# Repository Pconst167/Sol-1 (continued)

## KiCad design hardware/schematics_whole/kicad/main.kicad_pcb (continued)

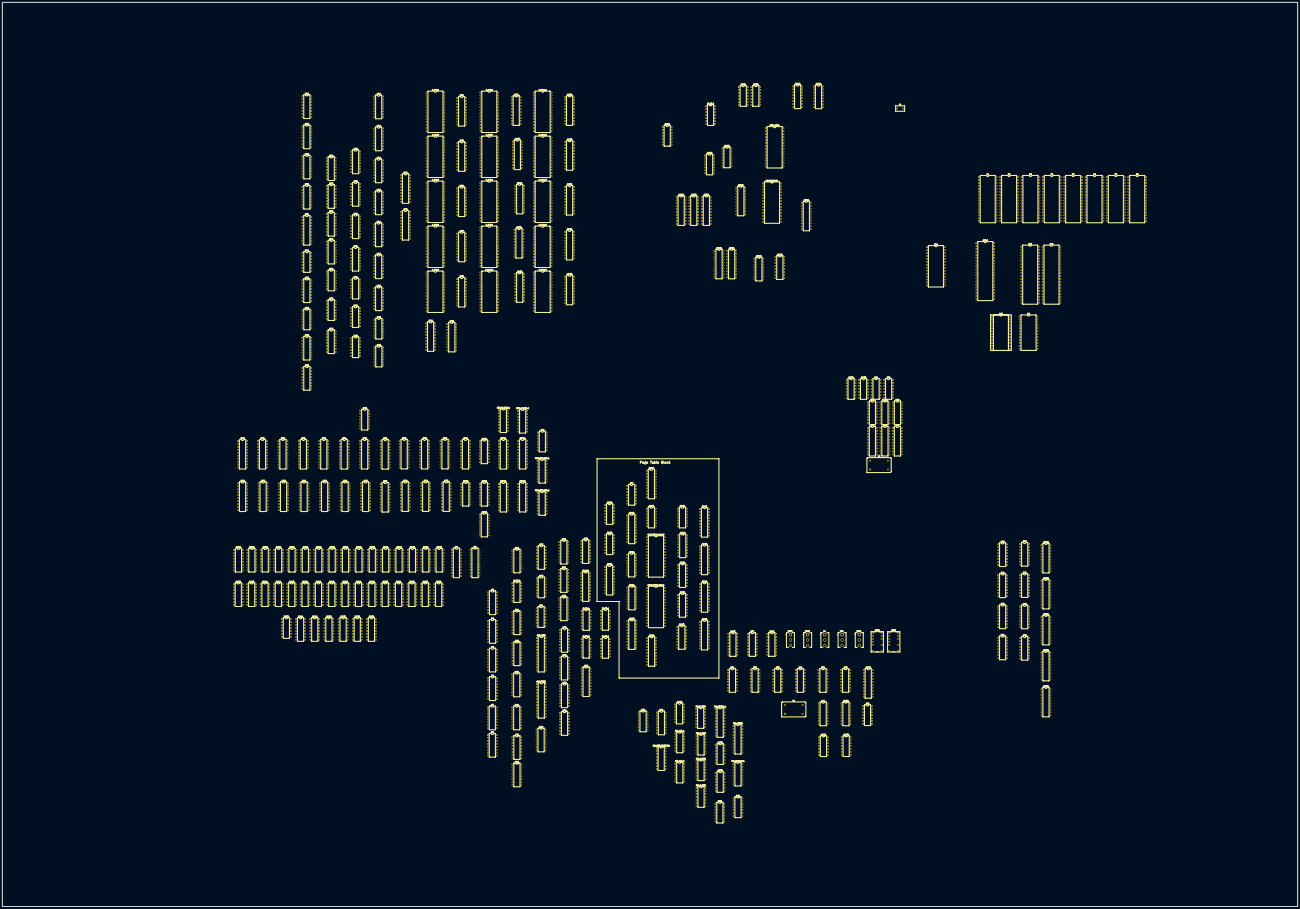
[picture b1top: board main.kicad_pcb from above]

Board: 2 copper layers, 1116.0 x 779.0 mm, 299 parts (0 on the bottom side), 1059 nets, no tracks yet.

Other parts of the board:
C1: C; C_Disc_D7.5mm_W4.4mm_P5.00mm
IC94, IC95: 74273N; DIP-20_W7.62mm
IC207, IC208: 7400N; DIP-14_W7.62mm

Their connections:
/int_status_0: IC207.2 (I1); also elsewhere on the board
/int_status_1: IC207.5 (I1); also elsewhere on the board
/int_status_2: IC207.10 (I1); also elsewhere on the board
/int_status_3: IC207.13 (I1); also elsewhere on the board
/int_status_4: IC208.2 (I1); also elsewhere on the board
/int_status_5: IC208.5 (I1); also elsewhere on the board
/int_status_6: IC208.10 (I1); also elsewhere on the board
/int_status_7: IC208.13 (I1); also elsewhere on the board
/irq_masks0: IC207.1 (I0); also elsewhere on the board
/irq_masks1: IC207.4 (I0); also elsewhere on the board
/irq_masks2: IC207.9 (I0); also elsewhere on the board
/irq_masks3: IC207.12 (I0); also elsewhere on the board
/irq_masks4: IC208.1 (I0); also elsewhere on the board
/irq_masks5: IC208.4 (I0); also elsewhere on the board
/irq_masks6: IC208.9 (I0); also elsewhere on the board
/irq_masks7: IC208.12 (I0); also elsewhere on the board
unnamed 536: IC94.3 (D1); also elsewhere on the board
unnamed 537: IC94.4 (D2); also elsewhere on the board
unnamed 538: IC94.7 (D3); also elsewhere on the board
unnamed 539: IC94.8 (D4); also elsewhere on the board
unnamed 540: IC94.13 (D5); also elsewhere on the board
unnamed 541: IC94.14 (D6); also elsewhere on the board
unnamed 542: IC94.17 (D7); also elsewhere on the board
unnamed 543: IC94.18 (D8); also elsewhere on the board
unnamed 544: IC95.3 (D1); also elsewhere on the board
unnamed 545: IC95.4 (D2); also elsewhere on the board
unnamed 546: IC95.7 (D3); also elsewhere on the board
unnamed 547: IC95.8 (D4); also elsewhere on the board
unnamed 548: IC95.13 (D5); also elsewhere on the board
unnamed 549: IC95.14 (D6); also elsewhere on the board
unnamed 550: IC95.17 (D7); also elsewhere on the board
cond_flag_src: IC95.6 (Q3); also elsewhere on the board
cond_invert: IC95.5 (Q2); also elsewhere on the board
cond_sel_0: IC95.9 (Q4); also elsewhere on the board
cond_sel_1: IC95.12 (Q5); also elsewhere on the board
cond_sel_2: IC95.15 (Q6); also elsewhere on the board
cond_sel_3: IC95.16 (Q7); also elsewhere on the board
rst: IC94.1 (CLR), IC95.1 (CLR); also elsewhere on the board
typ_0: IC94.2 (Q1); also elsewhere on the board
typ_1: IC94.5 (Q2); also elsewhere on the board
u_offset_0: IC94.6 (Q3); also elsewhere on the board
u_offset_1: IC94.9 (Q4); also elsewhere on the board
u_offset_2: IC94.12 (Q5); also elsewhere on the board
u_offset_3: IC94.15 (Q6); also elsewhere on the board
u_offset_4: IC94.16 (Q7); also elsewhere on the board
u_offset_5: IC94.19 (Q8); also elsewhere on the board
u_offset_6: IC95.2 (Q1); also elsewhere on the board
~clk: IC94.11 (CLK), IC95.11 (CLK); also elsewhere on the board

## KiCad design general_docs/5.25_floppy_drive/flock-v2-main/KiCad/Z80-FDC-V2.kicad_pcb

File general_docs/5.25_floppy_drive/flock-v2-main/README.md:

# Flock - Version 2.0
Floppy Disk Controller and Real Time Clock for RCBus systems

## Table of Content
* [Overview](#overview)
  * [Specifications](#specifications)
* [Assembly Instructions](#assembly-instructions)
* [Hardware Documentation](#hardware-documentation)
  * [Schematic and PCB Layout](#schematic-and-pcb-layout)
  * [Input/Output Ports](#inputoutput-ports)
  * [Connectors](#connectors)
  * [Bill of Materials](#bill-of-materials)
* [Release Notes](#release-notes)
  * [Changes](#changes)
  * [Known Issues](#known-issues)
* [Red Tape](#red-tape)
  * [Licensing](#licensing)
  * [Trademarks](#trademarks)

## Overview
Flock is an RCBus floppy disk controller (FDC) and real time clock (RTC) module. It designed to work with RomWBW firmware, supporting CP/M, ZSDOS, and various applications under these OSes.

### Specifications
* Floppy Disk Controller: Western Digital* WD37C65 or compatible
  * NEC uPD765 compatible with an integrated data separator, floppy interface drivers, and buffers
* Supported floppy disk formats:
  * 3.5", 720 KB
  * 3.5", 1.44 MB
  * 5.25", 360 KB diskettes in 360 MB drive
  * 5.25", 1.2 MB
  * 5.25", 360 KB diskettes in 1.2 MB drive (not supported by RomWBW, requires Y3, C10, and C11 to be installed)
* Supports two floppy drives, using IBM PC-like cable with twisted Disk Select / Motor Enable wires between two drives
* Real Time Clock: Maxim Integrated DS1302
* Bus: RCBus, RC2014* compatible

## Assembly Instructions

Please refer to [Assembly Instructions](Assembly_Instructions.md) document

## Hardware Documentation

### Schematic and PCB Layout

[Schematic - Version 2.0](KiCad/Z80-FDC-V2-Schematic-2.0.pdf)

[PCB Layout - Version 2.0](KiCad/Z80-FDC-V2-Board-2.0.pdf)

### Input/Output Ports

Flock uses the following I/O ports:

#### 0x48 - FDC CCR/DIR

Write: Floppy disk controller control configuration register (CCR)
Read: Floppy disk controller digital input register (DIR)

#### 0x50 - FDC MSR

Read: Floppy disk controller master status register (MSR)

#### 0x51 - FDC Data Register

Read/Write: Data from/to floppy disk controller

#### 0x58 - FDC DOR / TC

Write: Floppy disk controller digital output register (DOR)
Read: Toggle floppy disk controller transfer complete (TC) line

#### 0x0C or 0xC0 - RTC

Read/Write: Access real time clock (RTC)
The RTC address is configured using JP1 jumper

### Jumpers and Connectors

#### JP1 - RTC I/O address select

Position       | Description
-------------- | -----------------
open (default) | RTC address: 0xC0
closed         | RTC address: 0x0C

* Use 0xC0 address for Z80-based systems and 0x0C address for Z180-based systems

#### JP2 - Enable RTC

Position       | Description
-------------- | -----------------
1-2 (default)  | RTC enabled
2-3            | RTC disabled

* JP2 is a solder jumper, located on the back of the board
* By default positions 1-2 are connected with a PCB trace
* If the system already has an RTC or the RTC functionality is not needed:
  * Cut the PCB trace between positions 1-2
  * Connect positions 2-3 with a solder bridge

#### JP3 - Enable 300 Kbps transfer rate support

Position       | Description
-------------- | -----------------
1-2 (default)  | 300 Kbps disabled
2-3            | 300 Kbps enabled

* JP3 is a solder jumper, located on the back of the board
* By default positions 1-2 are connected with a PCB trace
* If 300 Kbps is desired:
  * Cut the PCB trace between positions 1-2
  * Connect positions 2-3 with a solder bridge
  * Install Y3, C10, and C11

#### J1 - Floppy
Connect to floppy drive interface connector.

Pin   | Signal Name | Description   | Pin   | Signal Name | Description
----- | ----------- | --------------| ----- | ----------- | -----------
J1-1  | GND         | Ground        | J1-2  | /DENSEL     | Density Select: 1 = Low density; 0 = High density
J1-3  | N/C         | Not connected | J1-4  | N/C         | Not connected
J1-5  | GND         | Ground        | J1-6  | N/C         | Not connected
J1-7  | GND         | Ground        | J1-8  | /INDEX      | Index hole: 0 = At the index hole
J1-9  | N/C         | Not connected | J1-10 | /MEA        | Motor Enable - Drive A
J1-11 | GND         | Ground        | J1-12 | /DSB        | Drive Select - Drive B
J1-13 | GND         | Ground        | J1-14 | /DSA        | Drive Select - Drive A
J1-15 | GND         | Ground        | J1-16 | /MEB        | Motor Enable - Drive B
J1-17 | N/C         | Not connected | J1-18 | /DIR        | Direction Select
J1-19 | GND         | Ground        | J1-20 | /STEP       | Head Step
J1-21 | GND         | Ground        | J1-22 | /WDATA      | Write Data
J1-23 | GND         | Ground        | J1-24 | /WE         | Write Enable: 0 = Write Enabled
J1-25 | GND         | Ground        | J1-26 | /TRK0       | Track 00: 0 = At the track 0
J1-27 | N/C         | Not connected | J1-28 | /WP         | Write Protect: 0 = Floppy disk is write protected
J1-29 | GND         | Ground        | J1-30 | /RDATA      | Read Data 
J1-31 | GND         | Ground        | J1-32 | /HDSEL      | Head Select / Side Select: 1 = Side 0; 0 = Side 1
J1-33 | N/C         | Not connected | J1-34 | /DC         | Disk changed: 1 = Disk changed; 0 = Ready

#### J2 - Floppy 5V
Connect to floppy 5V power supply connector.

**Important: J2 is an unfused 5V power supply for a single 3.5" floppy disk drive. Avoid overloading and short-circuiting**

Pin | Signal Name | Description
--- | ----------- | -----------
1   | 5V          | Positive terminal - +5V
2   | GND         | Negative terminal - ground

#### J3 - RCBus
Pin   | Signal Name | Description                             | Pin   | Signal Name | Description
----- | ----------- | --------------------------------------- | ----- | ----------- | -----------
J3-1  | A15         | Address A15; Input; Not connected       | J3-41 | p41         | Reserved; Not connected
J3-2  | A14         | Address A14; Input; Not connected       | J3-42 | /BAI        | Bus Acknowledge In; Not connected
J3-3  | A13         | Address A13; Input; Not connected       | J3-43 | /BAO        | Bus Acknowledge Out; Not connected
J3-4  | A12         | Address A12; Input; Not connected       | J3-44 | p44         | Reserved; Not connected
J3-5  | A11         | Address A11; Input; Not connected       | J3-45 | p45         | Reserved; Not connected
J3-6  | A10         | Address A10; Input; Not connected       | J3-46 | p46         | Reserved; Not connected
J3-7  | A9          | Address A9; Input; Not connected        | J3-47 | p47         | Reserved; Not connected
J3-8  | A8          | Address A8; Input; Not connected        | J3-48 | p48         | Reserved; Not connected
J3-9  | A7          | Address A7; Input                       | J3-49 | A23         | Address A23; Input; Not connected
J3-10 | A6          | Address A6; Input                       | J3-50 | A22         | Address A22; Input; Not connected
J3-11 | A5          | Address A5; Input                       | J3-51 | A21         | Address A21; Input; Not connected
J3-12 | A4          | Address A4; Input                       | J3-52 | A20         | Address A20; Input; Not connected
J3-13 | A3          | Address A3; Input                       | J3-53 | A19         | Address A19; Input; Not connected
J3-14 | A2          | Address A2; Input                       | J3-54 | A18         | Address A18; Input; Not connected
J3-15 | A1          | Address A1; Input                       | J3-55 | A17         | Address A17; Input; Not connected
J3-16 | A0          | Address A0; Input                       | J3-56 | A16         | Address A16; Input; Not connected
J3-17 | GND         | Ground                                  | J3-57 | GND         | Ground
J3-18 | VCC         | Power Supply - +5V                      | J3-58 | VCC         | Power Supply - +5V
J3-19 | /M1         | Machine Cycle One; Input                | J3-59 | /RFSH       | DRAM refresh; Input; Not connected
J3-20 | /RESET      | Reset; Input                            | J3-60 | PAGE        | Page ROM/RAM input; Not connected
J3-21 | CLK1        | CPU Clock; Input; Not connected         | J3-61 | CLK2        | UART Clock (programmable); Input; Not connected
J3-22 | /INT        | Interrupt; Output; Not connected        | J3-62 | /BUSACK     | DMA Bus Acknowledge; Input; Not connected
J3-23 | /MREQ       | Memory Request; Input; Not connected    | J3-63 | /HALT       | Halt; Input; Not connected
J3-24 | /WR         | Write Request; Input                    | J3-64 | /BUSREQ     | DMA Bus Request; Output; Not connected
J3-25 | /RD         | Read Request; Input                     | J3-65 | /WAIT       | Wait; Output; Not connected
J3-26 | /IORQ       | Input/Output Request; Input             | J3-66 | /NMI        | Non-maskable Interrupt; Output; Not connected
J3-27 | D0          | Data D0; Input/Output                   | J3-67 | D8          | Data D8; Input/Output; Not connected
J3-28 | D1          | Data D1; Input/Output                   | J3-68 | D9          | Data D9; Input/Output; Not connected
J3-29 | D2          | Data D2; Input/Output                   | J3-69 | D10         | Data D10; Input/Output; Not connected
J3-30 | D3          | Data D3; Input/Output                   | J3-70 | D11         | Data D11; Input/Output; Not connected
J3-31 | D4          | Data D4; Input/Output                   | J3-71 | D12         | Data D12; Input/Output; Not connected
J3-32 | D5          | Data D5; Input/Output                   | J3-72 | D13         | Data D13; Input/Output; Not connected
J3-33 | D6          | Data D6; Input/Output                   | J3-73 | D14         | Data D14; Input/Output; Not connected
J3-34 | D7          | Data D7; Input/Output                   | J3-74 | D15         | Data D15; Input/Output; Not connected
J3-35 | TX          | Channel 1, Transmit Data; Not Connected | J3-75 | TX2         | Channel 2, Transmit Data; Not Connected
J3-36 | RX          | Channel 1, Receive Data; Not Connected  | J3-76 | RX2         | Channel 2, Receive Data; Not Connected
J3-37 | /IRQ1       | Interrupt Request 1; Not connected      | J3-77 | /IRQ2       | Interrupt Request 2; Not connected
J3-38 | IEI         | Interrupt Enable In; Not connected      | J3-78 | p78         | Reserved; Not connected
J3-39 | IEO         | Interrupt Enable Out; Not connected     | J3-79 | p79         | Reserved; Not connected
J3-40 | USER4       | User Pin 4; Not connected               | J3-80 | USER8       | User Pin 8; Not connected

### Bill of Materials

#### Version 2.0

[Flock V2 project on Mouser.com](https://www.mouser.com/ProjectManager/ProjectDetail.aspx?AccessID=57797d9ea4) - View and order all components except of the FDC and the PCB.

[Flock project on OSH Park](https://oshpark.com/shared_projects/vQHiVNa8) - View and order the PCB.

Flock project on Tindie: [Complete kit](https://www.tindie.com/products/weird/flock-v2-rcbus-module-kit/); [Flock PCB and FDC](https://www.tindie.com/products/weird/flock-v2-rcbus-module-pcb-and-fdc/).

Component type     | Reference | Description                                 | Quantity | Possible sources and notes 
------------------ | --------- | ------------------------------------------- | -------- | --------------------------
PCB                |           | Flock PCB - Version 2.0                     | 1        | Buy from my Tindie store: [Complete kit](https://www.tindie.com/products/weird/flock-rcbus-v2-module-kit/); [Flock PCB and FDC](https://www.tindie.com/products/weird/flock-rcbus-v2-module-pcb-and-fdc/), or order from a PCB manufacturer of your choice using provided Gerber or KiCad files
Integrated Circuit | U1        | WD37C65BJM - FDC, CMOS, 44 pin PLCC         | 1        | eBay. Alternative: ST AIC37C65CL
Integrated Circuit | U2        | DS1302+ - RTC, 8 pin DIP                    | 1        | Mouser [700-DS1302](https://www.mouser.com/ProductDetail/700-DS1302)
Integrated Circuit | U3        | ATF16V8B-15PU - Simple Programmable Logic Device, 20 pin DIP | 1 | Mouser [556-AF16V8B15PU](https://www.mouser.com/ProductDetail/556-AF16V8B15PU)
Integrated Circuit | U4        | 74AHCT174 - Hex D-type flip-flop with reset, 16 pin DIP | 1 | Mouser [595-SN74AHCT174N](https://www.mouser.com/ProductDetail/595-SN74AHCT174N)
Integrated Circuit | U5        | 74HCT125 - Quadruple bus buffer gates with 3-state outputs, 14 pin DIP | 1 | Mouser [595-SN74HCT125NE4](https://www.mouser.com/ProductDetail/595-SN74HCT125NE4)
Quartz Crystal     | Y1        | 16 MHz, series                              | 1        | Mouser [774-ATS160-E](https://www.mouser.com/ProductDetail/774-ATS160-E)
Quartz Crystal     | Y2        | 32768 Hz, 6 pF                              | 1        | Mouser [815-AB26T32768KHZ6B](https://www.mouser.com/ProductDetail/815-AB26T32768KHZ6B)
Quartz Crystal     | Y3        | 9.6 MHz, series                             | 1        | Optional; Install for 300 Kbps transfer rate support
Connector          | J1        | 2x17 pin header, shrouded, 2.54 mm pitch, right angle | 1 | Mouser [517-30334-5002](https://www.mouser.com/ProductDetail/517-30334-5002)
Connector          | J2        | 2 pin header with friction lock, right angle | 1       | Mouser [571-2-644488-2](https://www.mouser.com/ProductDetail/571-2-644488-2)
Pin Header         | J3        | 2x40 pin header, 2.54 mm pitch, right angle | 1        | Mouser [517-5121TG](https://www.mouser.com/ProductDetail/517-5121TG)
Pin Header         | JP1       | 2 pin header, 2.54 mm pitch                 | 1        | Mouser [649-68002-102HLF](https://www.mouser.com/ProductDetail/649-68002-102HLF)
Jumper             | JP1       | Shunt, 2 pin 2.54 mm pitch                  | 1        | Mouser [806-SX1100-B](https://www.mouser.com/ProductDetail/806-SX1100-B)
Battery Holder     | BT1       | CR2032 battery holder                       | 1        | Mouser [122-2620-GR](https://www.mouser.com/ProductDetail/122-2620-GR) or [122-2420-GR](https://www.mouser.com/ProductDetail/122-2420-GR). Install either BT1 or C7
Battery            | BT1       | CR2023 battery                              | 1        | Mouser [81-CR2032](https://www.mouser.com/ProductDetail/81-CR2032), [658-CR2032](https://www.mouser.com/ProductDetail/658-CR2032), or [614-CR2032-200](https://www.mouser.com/ProductDetail/614-CR2032-200). Install either BT1 or C7
Capacitor          | C1 - C5   | 0.1 uF, 50V, MLCC, 5 mm pitch               | 5        | Mouser [810-FG28X7R1H104KNT6](https://www.mouser.com/ProductDetail/810-FG28X7R1H104KNT6)
Capacitor          | C6        | 10 uF, 47V, Organic Polymer, 6.3 mm diameter, 2.5 mm pitch | 1 | Mouser [80-A759EA106M1JAAE60](https://www.mouser.com/ProductDetail/80-A759EA106M1JAAE60). Note: PCB silkscreen specifies 47uF capacitor. 10uF - 47uF capacitor with voltage rating 10V or more can be used
Capacitor          | C7        | 0.22 F, 5.5V, Supercapacitor, 13.5 mm diameter, 5 mm pitch | 1 | Mouser [555-DBN-5R5D334T](https://www.mouser.com/ProductDetail/555-DBN-5R5D334T). Install either BT1 or C7
Capacitor          | C8        | 47 pF, 50V, MLCC, 5 mm pitch                | 1        | Mouser [810-FG28C0G2A470JNT0](https://www.mouser.com/ProductDetail/810-FG28C0G2A470JNT0)
Capacitor          | C9        | 15 pF, 50V, MLCC, 5 mm pitch                | 1        | Mouser [810-FG28C0G2A150JNT0](https://www.mouser.com/ProductDetail/810-FG28C0G2A150JNT0)
Capacitor          | C10       | 68 pF, 50V, MLCC, 5 mm pitch                | 1        | Optional; Install for 300 Kbps transfer rate support
Capacitor          | C11       | 56 pF, 50V, MLCC, 5 mm pitch                | 1        | Optional; Install for 300 Kbps transfer rate support
Resistor Array     | RN1       | 1 kohm, bussed, 6 pin SIP                   | 1        | Mouser [652-4606X-1LF-1K](https://www.mouser.com/ProductDetail/652-4606X-1LF-1K)
Resistor           | R1 - R3   | 10 kohm, 0.25 W, 1% tolerance, axial        | 3        | Mouser [603-MFR-25FRF5210K](https://www.mouser.com/ProductDetail/603-MFR-25FRF5210K)
IC Socket          | U1        | 44 pin PLCC, through hole                   | 1        | Mouser [649-54020-44030LF](https://www.mouser.com/ProductDetail/649-54020-44030LF), [517-8444-11B1-RK-TP](https://www.mouser.com/ProductDetail/517-8444-11B1-RK-TP)
IC Socket          | U2        | 8 pin DIP                                   | 1        | Mouser [649-DILB8P223TLF](https://www.mouser.com/ProductDetail/649-DILB8P223TLF)
IC Socket          | U3        | 20 pin DIP                                  | 1        | Mouser [649-DILB20P-223TLF](https://www.mouser.com/ProductDetail/649-DILB20P-223TLF)
IC Socket          | U4        | 16 pin DIP                                  | 1        | Mouser [649-DILB16P-223TLF](https://www.mouser.com/ProductDetail/649-DILB16P-223TLF)
IC Socket          | U5        | 14 pin DIP                                  | 1        | Mouser [649-DILB14P-223TLF](https://www.mouser.com/ProductDetail/649-DILB14P-223TLF)
Connector          | J2        | 2 pin connector                             | 1        | Mouser [571-3-643813-2](https://www.mouser.com/ProductDetail/571-3-643813-2)
Connector          | J2        | Floppy disk power connector housing         | 1        | Mouser [571-1718224](https://www.mouser.com/ProductDetail/571-1718224)
Connector          | J2        | Floppy disk power connector contacts        | 2        | Mouser [571-170262-2-LP](https://www.mouser.com/ProductDetail/571-170262-2-LP), [571-1702622-CT](https://www.mouser.com/ProductDetail/571-1702622-CT) (strip of 100 contacts)

## Release Notes

### Changes

* Version 2.0
  * Update form factor from RC2014* compatible to RCBus
  * Add an option to use CR2032 battery instead of a super capacitor for the RTC
  * Use right angle connector for the floppy interface
  * Use ATF16V8B SPLD for address decode
  * Add JP1 jumper for selecting RTC I/O address. Either 0xC0 or 0x0C can be used
  * Add JP2 jumper for disabling the RTC.
  * Add an option to support 300 Kbps transfer speed
  * Add a header for GPIO signals
* Version 1.0
  * Initial version

### Known Issues

* Version 1.0
  * No known issues

### Wishlist
* None so far

## Red Tape

### Licensing

Flock is an open source hardware project certified by [Open Source Hardware Association](https://www.oshwa.org/), certification UID is [US002115](https://certification.oshwa.org/us002115.html). The hardware design itself, including schematic and PCB layout design files are licensed under the strongly-reciprocal variant of [CERN Open Hardware Licence version 2](license-cern_ohl_s_v2.txt). The CPLD VHDL code is licensed under [GNU General Public License v3](license-gpl-3.0.txt). Documentation, including this file, is licensed under the [Creative Commons Attribution-ShareAlike 4.0 International License](license-cc-by-sa-4.0.txt).

### Trademarks

* "RC2014" is a registered trademark of RFC2795 Ltd.
* Other names and brands may be claimed as the property of others.

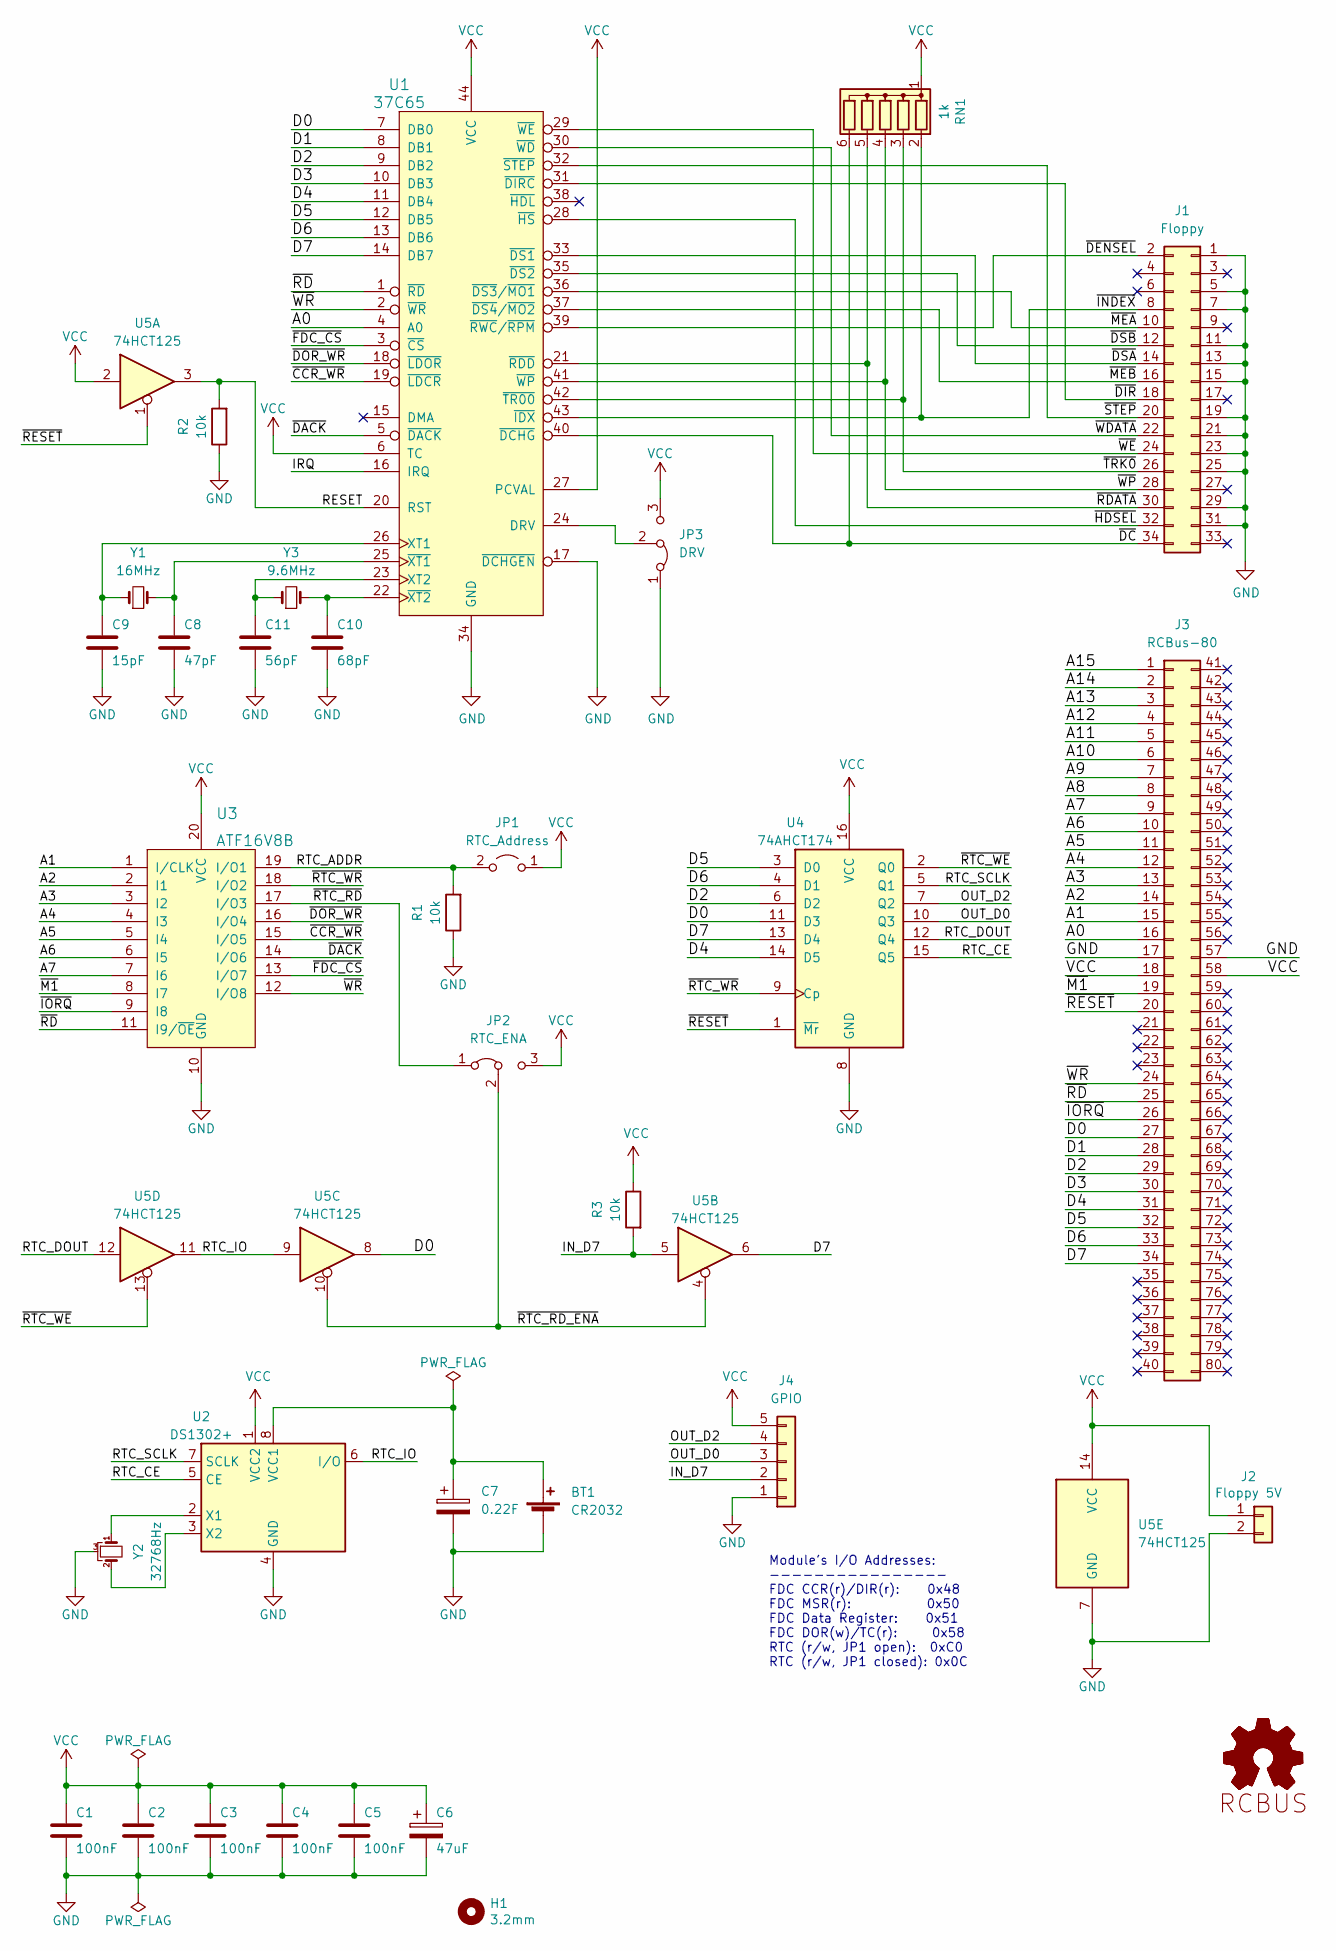
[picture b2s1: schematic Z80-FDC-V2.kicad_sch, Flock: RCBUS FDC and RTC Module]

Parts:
BT1: CR2032; Battery_Holder_CR2032_Universal
C1, C2, C3, C4, C5: 100nF; Cap_Cer_508
C6: 47uF; Cap_Elec_Radial_6.3mm
C7: 0.22F; Cap_Super_Radial_13.5mm
C8: 47pF; Cap_Cer_508
C9: 15pF; Cap_Cer_508
C10: 68pF; Cap_Cer_508
C11: 56pF; Cap_Cer_508
H1: 3.2mm; MountingHole_3.2mm_M3_DIN965
J1: Floppy; Conn_Pin_Header_17x2_2.54mm_Shrouded_RA
J2: Floppy 5V; Conn_TE_2-644488-2_2P_2.54mm
J3: RCBus-80; Conn_Pin_Header_40x2_2.54mm_Right_Angle_RCBus80
J4: GPIO; Conn_Pin_Header_5x1_2.54mm
JP1: RTC_Address; Conn_Pin_Header_2x1_2.54mm_NoKey
JP2: RTC_ENA; SolderJumper-3_P1.3mm_Bridged12_RoundedPad1.0x1.5mm_NumberL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
JP3: DRV; SolderJumper-3_P1.3mm_Bridged12_RoundedPad1.0x1.5mm_NumberL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
LOGO1, LOGO2: Logo_Open_Hardware_Small; OSHW-Logo_5.7x6mm_SilkScreen
LOGO3: RCBUS_Logo
R1, R2, R3: 10k; Res_762
RN1: 1k; Conn_SIL6
U1: 37C65; IC_PLCC44_TH
U2: DS1302+; IC_DIP8_300
U3: ATF16V8B; IC_DIP20_300
U4: 74AHCT174; IC_DIP16_300
U5: 74HCT125; IC_DIP14_300
Y1: 16MHz; Crystal_HC-49U_Vert
Y2: 32768Hz; Crystal_32K_Horiz
Y3: 9.6MHz; Crystal_HC-49U_Vert

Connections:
/A0: J3.16, U1.4 (A0)
/A1: J3.15, U3.1 (I/CLK)
/A2: J3.14, U3.2 (I1)
/A3: J3.13, U3.3 (I2)
/A4: J3.12, U3.4 (I3)
/A5: J3.11, U3.5 (I4)
/A6: J3.10, U3.6 (I5)
/A7: J3.9, U3.7 (I6)
/A8: J3.8
/A9: J3.7
/A10: J3.6
/A11: J3.5
/A12: J3.4
/A13: J3.3
/A14: J3.2
/A15: J3.1
/D0: J3.27, U1.7 (DB0), U4.11 (D3), U5.8
/D1: J3.28, U1.8 (DB1)
/D2: J3.29, U1.9 (DB2), U4.6 (D2)
/D3: J3.30, U1.10 (DB3)
/D4: J3.31, U1.11 (DB4), U4.14 (D5)
/D5: J3.32, U1.12 (DB5), U4.3 (D0)
/D6: J3.33, U1.13 (DB6), U4.4 (D1)
/D7: J3.34, U1.14 (DB7), U4.13 (D4), U5.6
/IN_D7: J4.2, R3.2, U5.5
/IRQ: U1.16 (IRQ)
/OUT_D0: J4.3, U4.10 (Q3)
/OUT_D2: J4.4, U4.7 (Q2)
/RESET: R2.2, U1.20 (RST), U5.3
/RTC_ADDR: JP1.2 (B), R1.2, U3.19 (I/O1)
/RTC_CE: U2.5 (CE), U4.15 (Q5)
/RTC_DOUT: U4.12 (Q4), U5.12
/RTC_IO: U2.6 (I/O), U5.9, U5.11
/RTC_SCLK: U2.7 (SCLK), U4.5 (Q1)
/~CCR_WR: U1.19 (~LDCR), U3.15 (I/O5)
/~DACK: U1.5 (~DACK), U3.14 (I/O6)
/~DC: J1.34, RN1.6 (R5), U1.40 (~DCHG)
/~DENSEL: J1.2, U1.39 (~RWC/~RPM)
/~DIR: J1.18, U1.31 (~DIRC)
/~DOR_WR: U1.18 (~LDOR), U3.16 (I/O4)
/~DSA: J1.14, U1.33 (~DS1)
/~DSB: J1.12, U1.35 (~DS2)
/~FDC_CS: U1.3 (~CS), U3.13 (I/O7)
/~HDSEL: J1.32, U1.28 (~HS)
/~INDEX: J1.8, RN1.2 (R1), U1.43 (~IDX)
/~IORQ: J3.26, U3.9 (I8)
/~M1: J3.19, U3.8 (I7)
/~MEA: J1.10, U1.36 (~DS3/~MO1)
/~MEB: J1.16, U1.37 (~DS4/~MO2)
/~RDATA: J1.30, RN1.5 (R4), U1.21 (~RDD)
/~RD: J3.25, U1.1 (~RD), U3.11 (I9/~OE)
/~RESET: J3.20, U4.1 (~Mr), U5.1
/~RFSH: J3.59
/~RTC_RD_ENA: JP2.2 (C), U5.4, U5.10
/~RTC_RD: JP2.1 (A), U3.17 (I/O3)
/~RTC_WE: U4.2 (Q0), U5.13
/~RTC_WR: U3.18 (I/O2), U4.9 (Cp)
/~STEP: J1.20, U1.32 (~STEP)
/~TRK0: J1.26, RN1.3 (R2), U1.42 (~TR00)
/~WDATA: J1.22, U1.30 (~WD)
/~WE: J1.24, U1.29 (~WE)
/~WP: J1.28, RN1.4 (R3), U1.41 (~WP)
/~WR: J3.24, U1.2 (~WR), U3.12 (I/O8)
GND: BT1.2 (-), C1.2, C2.2, C3.1, C4.2, C5.2, C6.2, C7.2, C8.2, C9.2, C10.2, C11.2, J1.1, J1.5, J1.7, J1.11, J1.13, J1.15, J1.19, J1.21, J1.23, J1.25, J1.29, J1.31, J2.2, J3.17, J3.57, J4.1, JP3.1 (A), R1.1, R2.1, U1.17 (~DCHGEN), U1.34 (GND), U2.4 (GND), U3.10 (GND), U4.8 (GND), U5.7 (GND), Y2.3
unnamed: BT1.1 (+), C7.1, U2.8 (VCC1)
unnamed: C8.1, U1.25 (~XT1), Y1.2
unnamed: C9.1, U1.26 (XT1), Y1.1
unnamed: C10.1, U1.22 (~XT2), Y3.2
unnamed: C11.1, U1.23 (XT2), Y3.1
unnamed: JP3.2 (C), U1.24 (DRV)
unnamed: U2.2 (X1), Y2.1
unnamed: U2.3 (X2), Y2.2
VCC: C1.1, C2.1, C3.2, C4.1, C5.1, C6.1, J2.1, J3.18, J3.58, J4.5, JP1.1 (A), JP2.3 (B), JP3.3 (B), R3.1, RN1.1 (common), U1.6 (TC), U1.27 (PCVAL), U1.44 (VCC), U2.1 (VCC2), U3.20 (VCC), U4.16 (VCC), U5.2, U5.14 (VCC)

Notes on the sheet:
Module's I/O Addresses: ---------------- FDC CCR(r)/DIR(r): 0x48 FDC MSR(r): 0x50 FDC Data Register: 0x51 FDC DOR(w)/TC(r): 0x58 RTC (r/w, JP1 open): 0xC0 RTC (r/w, JP1 closed): 0x0C

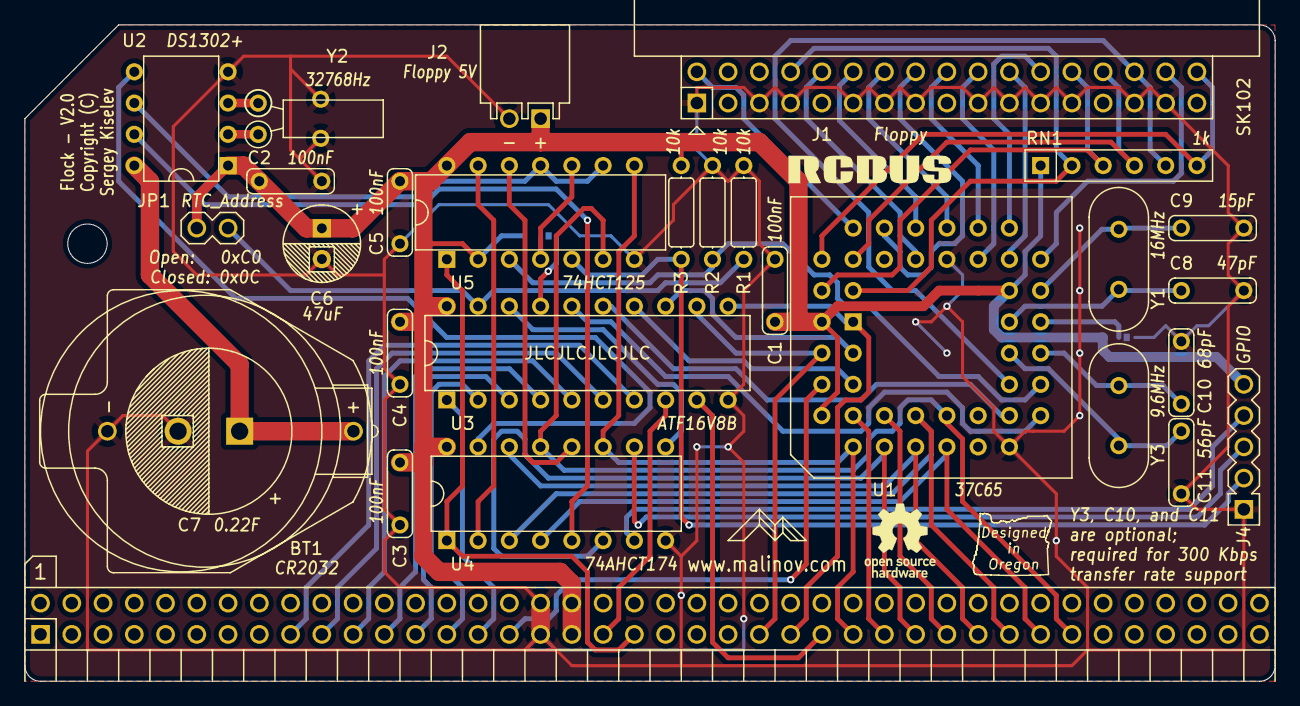
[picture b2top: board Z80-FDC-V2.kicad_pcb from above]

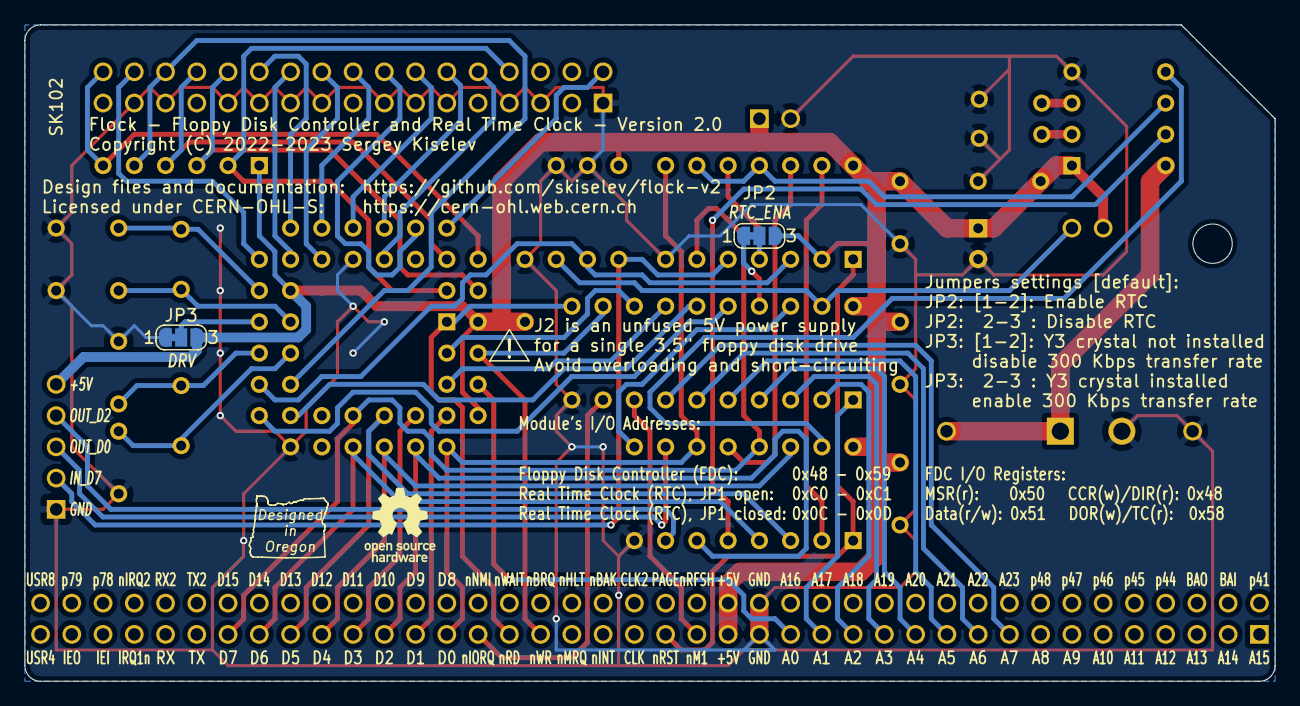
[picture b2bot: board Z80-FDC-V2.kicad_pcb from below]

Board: 2 copper layers, 101.6 x 53.3 mm, 35 parts (3 on the bottom side), 63 nets.

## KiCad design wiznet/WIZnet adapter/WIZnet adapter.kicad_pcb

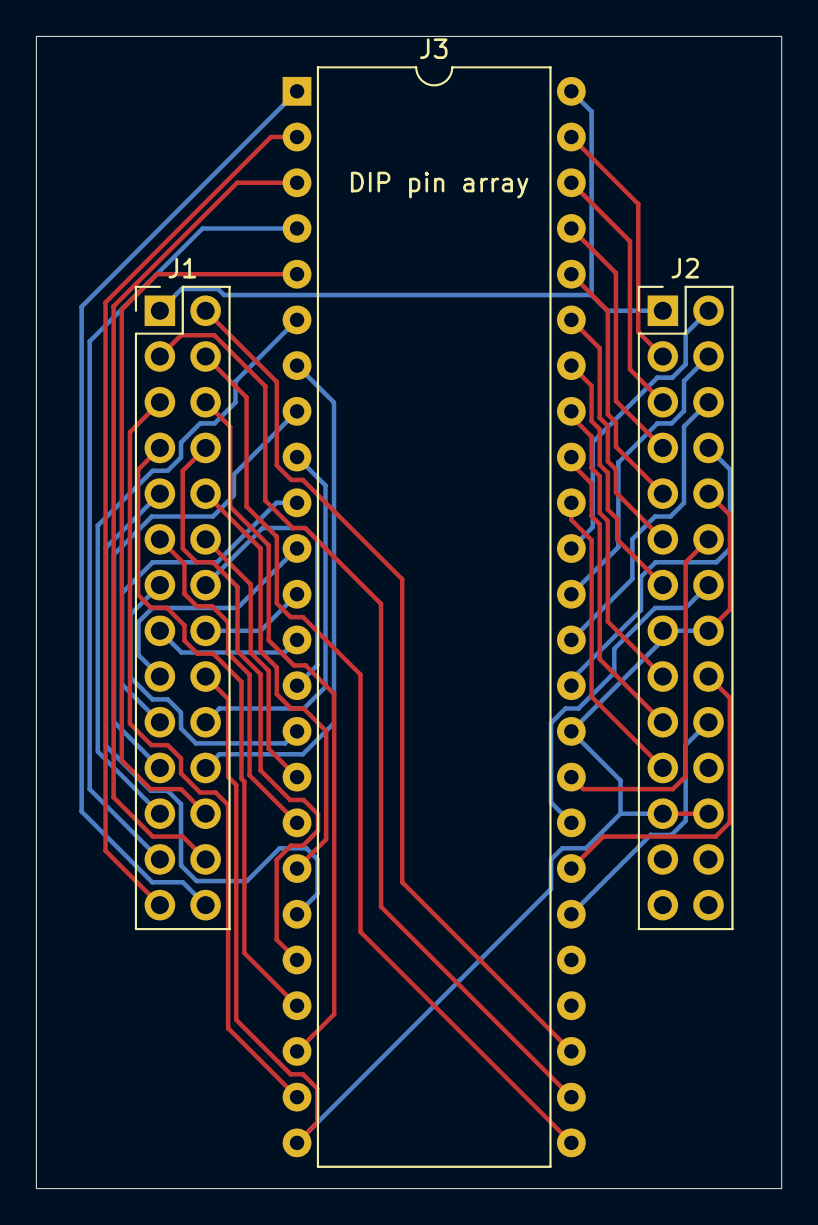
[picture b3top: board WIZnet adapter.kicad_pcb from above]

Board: 2 copper layers, 41.4 x 64.0 mm, 3 parts (0 on the bottom side), 45 nets.

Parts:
J1, J2: Conn_02x14_Odd_Even; PinHeader_2x14_P2.54mm_Vertical
J3: DIP pin array; DIP-48_W15.24mm

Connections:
A0: J1.28, J3.1
A1: J1.27, J3.2
A2: J1.26, J3.3
A3: J1.25, J3.4
A4: J1.24, J3.5
A5: J1.23, J3.6
A6: J1.22, J3.7
A7: J1.21, J3.8
A8: J1.20, J3.9
A9: J1.19, J3.10
BIT16EN: J2.2, J3.38
BRDY0: J2.14, J3.32
BRDY1: J2.13, J3.42
BRDY2: J2.12, J3.33
BRDY3: J2.11, J3.43
D0: J1.17, J3.11
D1: J1.16, J3.12
D2: J1.15, J3.13
D3: J1.14, J3.14
D4: J1.13, J3.15
D5: J1.12, J3.16
D6: J1.11, J3.17
D7: J1.10, J3.18
D8: J1.9, J3.19
D9: J1.8, J3.20
D10: J1.7, J3.21
D11: J1.6, J3.22
D12: J1.5, J3.23
D13: J1.4, J3.25
D14: J1.3, J3.26
D15: J1.2, J3.27
GND: J1.18, J2.10, J2.15, J2.16, J2.23, J2.24, J3.24, J3.34
Vcc: J1.1, J2.1, J3.48
~ACTLED: J2.9, J3.44
~COLLED: J2.6, J3.36
~CS: J2.19, J3.40
~FDXLED: J2.7, J3.45
~INT: J2.18, J3.31
~LINKLED: J2.3, J3.47
~RD: J2.20, J3.30
~RESET: J2.17, J3.41
~RXLED: J2.5, J3.46
~SPDLED: J2.8, J3.35
~TXLED: J2.4, J3.37
~WR: J2.21, J3.39

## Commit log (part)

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2024-06-24 micro
2024-06-25 sand32 sor32 add32 adc32 sub32 sbb32 and others added
2024-06-28 fix sor/sand.
2024-06-28 fix shl32
2024-06-28 add cmp32 cb, i32
2024-06-28 working on 32bit inc/dec
2024-07-06 socat
2024-07-06 software
2024-07-06 soft
2024-07-14 cleanup
2024-07-15 added notes
2024-07-16 floppy docs
2024-07-16 add vm fig
2024-07-16 added inline asm
2024-07-16 update schem
2024-07-16 floppy
2024-07-17 docs
2024-07-17 change dirs
2024-07-17 added various games
2024-07-17 adding smallc and cpm to misc
2024-07-18 add tms2797 datasheet
2024-07-18 writing list of sol-1 cpu improvements for next version
2024-07-18 flppy
2024-07-22 floppy notes
2024-07-25 notes
2024-08-19 floppy drive
2024-10-03 esp8266
2024-10-25 fpu updates
2025-11-23 nothing
2025-12-13 for post inc/dec the var address was being generated twice. removed one of the generations.
2025-12-24 adding note about fs
2025-12-28 file system ext2
2026-01-02 adding new bootloader for ext2 fs
2026-01-02 adding new kernel for ext2 fs
2026-01-06 ext2
2026-01-08 start work on ls syscall
2026-01-08 adding comment
2026-01-11 fixing calculation for inode sector and offet
2026-01-13 adding attribute to struct to remove padding
2026-01-13 adding attribute to remove padding
2026-01-13 renaming files
2026-01-13 add comments
2026-01-16 fixing bug on kernel loading
2026-01-18 hurry and commit thisgit add -A! after 2 days debugging i find my code misbehaves because of single offset bytes generated by solfs.
2026-01-22 software build script moves .exp to ./lib
2026-01-22 adding comments for process/file descriptors
2026-01-22 add uart1
2026-01-23 add kernel notes
2026-01-23 decrease kernel binary size by removing static data from temporary areas, by uisng $
2026-01-23 clean up
2026-01-23 adding file obj and proc tables
2026-01-23 proc syscall
2026-01-26 pid control
2026-01-26 fork syscall
2026-01-28 fork
2026-01-28 copy parent image into child
2026-01-28 add proc memory mapper
2026-03-13 readme
2026-03-13 removing misc textfiles
2026-04-29 improve emulator with -O3 flag

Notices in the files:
general_docs/5.25_floppy_drive/flock-v2-main/KiCad/Z80-FDC-V2.kicad_pcb:
Licensed under CERN-OHL-S: https://cern-ohl.web.cern.ch
Copyright (C) 2022-2023 Sergey Kiselev
Copyright (C)
general_docs/5.25_floppy_drive/flock-v2-main/README.md:
CERN-OHL-2.0-S, GPL-3.0, CC-BY-SA-4.0
